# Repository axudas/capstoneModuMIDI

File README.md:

# ModuMIDI 2: Hall-Effect MIDI Keyboard (Capstone)

A modular MIDI keyboard that uses **magnetic (hall-effect) key switches** for analog, velocity-sensitive key sensing. The keyboard is built from identical 30-key **banks** that butt together flush, with the key pitch running straight across each seam. Each bank has its own RP2350 that reads its 30 sensors; a head unit (Adafruit Metro RP2350 with a 2.0" ST7789 display, encoder and buttons) collects the banks and sends USB-MIDI. This project builds on the original ModuMIDI (see `reference/original-modumidi`).

Portfolio page: [aidancarr.tech/modumidi.html](https://aidancarr.tech/modumidi.html)

## Repository layout

```
capstone/
├── README.md
├── design-notes.md            key design decisions and numbers
├── hardware/
│   ├── bank-board/            KiCad bank board (one per bank, 30 sensors, RP2350)
│   ├── bank-plate/            bank switch plate: laser-cut SVG, STEP, FreeCAD
│   ├── key-prototype/         one-key test stacks for the 3u white / black / grey keys: KiCad board, 3D models
│   ├── switch-test-rig/       FreeCAD switch-lifetime test rig (macro, FCStd, STEP, STLs)
│   └── kicad-library/         Capstone_Keyboard KiCad symbols, footprints, 3D models
├── firmware/                  firmware (bank firmware not started)
└── reference/
    └── original-modumidi/     original ModuMIDI: Altium PCB, 3D-printed parts, photos
```

## Status

| Area | Status |
|---|---|
| Parts library (KiCad) | ✅ Done. Needs a 1:1 paper-print fit check |
| Bank plate | ✅ Designed (SVG / STEP / FCStd), not cut yet |
| Bank board: schematic | 🟡 Complete first pass, all wired: RP2350A + flash, 12 V → 5 V → 3.3 V power, 4 analog muxes, 30 key-link connectors (LED chain + key presence), RS-485 bus. Netlist checked; ERC in KiCad 10 still to run |
| Bank board: layout | 🟡 Stepped bank outline, 6 mounting holes, all 214 parts placed (sensors, their capacitors and the key connectors on top; everything else on the bottom). Not routed |
| Head unit | 🟡 Metro RP2350 + display on the bench (see the design notebook); no board yet |
| Key prototype (1 key, 3u, RGB; white / black / grey) | 🟡 Shared board routed (DRC clean), models + cut files for all three keys, not built |
| Switch test rig | ✅ Designed, ready to print (servo dimensions need measuring) |
| Firmware | 🟡 Head-unit bring-up and 31-EDO MPE output tested (design notebook); bank firmware not started, nothing in `firmware/` yet |
| Enclosure / keycaps | ⬜ Not started |

## What's in each part

### Bank layout
Each bank has 30 keys in three rows (white at the front, black in the middle, grey at the back), 10 columns at a **22.86 mm (0.900 in)** pitch, with 3u stabilizers whose wires run front to back (14 × 7 mm housings). The rows are 48.90 mm apart so the white-rear / black-front and black-rear / grey-front housings sit side by side without touching. Banks repeat every **228.60 mm (9.000 in)**. A straight seam would cut through a cut-out, so the side edges have one step: a tab on the left drops into a notch on the right of the next bank. Details are in [design-notes.md](design-notes.md).

### Bank plate: `hardware/bank-plate`
1.5 mm switch plate for one bank (240.03 × 180.34 mm) with the stepped tab and notch, 30 switch cut-outs, 60 stabilizer cut-outs and 8 M3 holes. See its [README](hardware/bank-plate/README.md).

### Bank board: `hardware/bank-board`
One board per bank, shaped like the bank outline and trimmed front and back to the sensors and mounting holes (239.53 × 104.18 mm). 30 pick-and-place **DRV5055A4** hall sensors (SOT-23) sit under the switch centres and go through four analog muxes into the bank's own **RP2350A**. The board makes its own 5 V and 3.3 V from the 12 V on the inter-bank connector and talks to the head unit over RS-485. See its [README](hardware/bank-board/README.md) for every part and why it's there.

### Parts library: `hardware/kicad-library`
Custom KiCad symbols and footprints: RP2350A (QFN-60, from Raspberry Pi's reference design), hall sensors (SOT-23 and TO-92), magnetic MX switch, Cherry stabilizer holes, barrel jack, EC11 encoder, tactile switch, Metro RP2350 shield headers, ST7789 display header. Both KiCad projects already point to it. See its [README](hardware/kicad-library/README.md).

### Key prototype: `hardware/key-prototype`
Single-key test stacks for the three 3u bank keys (white, black, grey): one hand-solderable board shared by all three, foam, an acrylic plate with the bank plate's switch cut-out and Gateron low-profile stabilizer cut-outs (6.25u stabilizers, wire bent to 3u), a key with an LED pixel, and a magnetic diffuser topper with a top-detect pogo contact. See its [README](hardware/key-prototype/README.md).

### Switch lifetime test rig: `hardware/switch-test-rig`
A 3D-printable rig that presses a switch straight down over and over to measure its lifetime: micro servo, 2:1 gears, cam, roller and guided plunger. See its [README](hardware/switch-test-rig/README.md).

## Next steps

**Electronics**
- [ ] Fit-check the library footprints: print them 1:1 and push the real parts through.
- [ ] Run ERC on the bank schematic in KiCad 10.
- [ ] Choose the key-base wiring (flex or wires) and the blind-mate inter-bank header; both have placeholder footprints.
- [ ] Route the bank board, run DRC and order boards.
- [ ] Head-unit side of the bus: an RS-485 transceiver with fail-safe bias resistors.
- [ ] Check that the inner stabilizer housings clear the board under the plate (cut-outs in the board, or enough plate-to-PCB height).

**Firmware (`firmware/`)**
- [ ] Read the sensors through the muxes and calibrate each key (rest / bottom-out).
- [ ] Turn key travel into MIDI note on/off with velocity (and optionally aftertouch).
- [ ] MIDI output, display UI and encoder menu.

**Mechanical**
- [ ] Cut a bank plate and test the switch fit and the tab/notch tiling.
- [ ] Design the enclosure (it must follow the stepped plate profile) and the keycaps.
- [ ] Build the key prototypes (white, black, grey), measure a real Gateron low-profile stabilizer, and test its 12.5 × 6 mm cut-out and bent wire. Then update the bank plate's stabilizer cut-outs to match.

**Testing**
- [ ] Measure the SG51R servo, update the rig macro, then print and build the test rig.
- [ ] Write test-rig firmware (servo cycling, press counter, sensor logging) and run lifetime tests.

## Tools

- [KiCad](https://www.kicad.org) 10: schematics, boards and the parts library. Open `hardware/bank-board/moduMidi.kicad_pro` or `hardware/key-prototype/pcb/spacebarHall.kicad_pro`; the library tables are already set up.
- [FreeCAD](https://www.freecad.org) 1.1: bank plate and test rig.
- Python (manifold3d, trimesh, pyvista): key prototype models and renders.

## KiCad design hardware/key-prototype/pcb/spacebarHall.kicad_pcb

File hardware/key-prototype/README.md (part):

# Key prototype: one hall-effect key, 3u, RGB-lit (white / black / grey)

A single-key test stack for the ModuMIDI 2 bank keys. Each of the three key types has its own set of files: **white** (wide head at the front, narrow tail running back), **black** (narrow, centred on its switch) and **grey** (the white key turned around, head at the back). All three use the same board, switch, stabilizer and layer heights as the bank, and the plate cut-outs match [`bank-plate/ModuMIDI2_bank_plate.svg`](../bank-plate/README.md).

- A magnetic MX-style switch sits under the key, with a **Gateron low-profile plate-mounted stabilizer** (bought as 6.25u, wire cut and bent to 3u) whose housings are 19.05 mm in front of and behind the switch. The key runs front to back.
- One RGB pixel cut from a 5 mm WS2812B-2020 strip sits in a pocket in the key and shines up into a thin, hollow, diffusing topper.
- The topper locates with a lip all round that hugs the top of the key, and is held on by two magnets.
- A 2-pin pogo connector in the key is shorted by a brass shim in the topper, so the controller can tell whether the topper is on.
- Everything on the board is **hand-solderable** through-hole.

Each stack on its own: [white](img/exploded_white.png), [black](img/exploded_black.png), [grey](img/exploded_grey.png).

## Key sizes

Cap outlines from the bank drawing, measured from the key's switch centre (y = toward the back):

| Key | Outline | Switch |
|---|---|---|
| White | Head 20.32 mm wide from y −28.58 to +17.78, tail 6.35 mm wide from +17.78 to +47.63 (76.2 mm long) | 28.58 mm from the front end |
| Black | 11.43 × 57.15 mm, y −28.58 to +28.58 | centred |
| Grey | The white key turned 180°: head from −17.78 to +28.58, tail from −47.63 to −17.78 | 28.58 mm from the back end |

All keys are 12 mm tall with steep walls (the top is 0.6 mm in from the bottom edge all round).

## Layer stack (bottom → top)

| # | Layer | Size | Notes |
|---|---|---|---|
| 1 | **PCB** | 1.6 mm | 30 × 113 mm, shared by all three keys. **U1** TO-92 hall sensor lies flat under the switch centre. **C1** 100 nF axial. **R1** 330 Ω (LED data), **R3** 10 kΩ pull-up (top detect). **J2** 5-pin key header 11.35 mm behind the switch (DI, DET, GND, DO, 5V: the five wires up to the key). **J1** 7-way 3.5 mm screw terminal on a 13 mm tab that sticks out past the foam and plate. |
| 2 | **Foam** | 3.5 mm | Fills the gap between PCB and plate. Cut-outs for the switch, stabilizer housings, wire and wire arms, C1/R1/R3, and the J2 header. |
| 3 | **Acrylic plate** | 1.5 mm | 14.00 mm switch cut-out and two **12.5 × 6.0 mm** low-profile stabilizer cut-outs (Gateron's drawing) 19.05 mm in front of and behind it. **A 1.7 mm slot for the stabilizer wire** runs from each housing's notch out to the bar and along the bar, 9.5 mm to the side of the switch (a U joining the two housings): the wire drops into the slot, the bar pivots there and the arms go through the notches into the sliders. Plus a 12.7 × 2.6 mm slot over J2 for the key's five wires. Each opening is one closed outline in the DXF. |
| 4 | **Key** | 12 mm tall | Centre MX stem socket, and 2 **stabilizer posts** on the centre line that reach down to the low-profile stabilizer (it sits much lower than the full-height switch; the posts stick out below the narrow white/grey tail). On top: **LED pocket** (strip piece + wire bay over the wire hole), **pogo connector pocket** (pins up), **2 magnet pockets**. Underneath: a relief for the switch top housing (the black key is narrower than the switch). |
| 4a | **RGB LED** | 5 × 6.9 mm | **One pixel cut from a 5 mm wide, 144 LED/m WS2812B-2020 strip.** Solder DI, 5V and GND to its DIN-end pads and DO to its DOUT-end pad (lay the DO wire back along the edge of the strip, beside the LED body, to the wire bay). All wires drop through the key's wire hole and the plate slot to J2. |
| 4c | **Pogo connector** | 9.6 × 3.2 mm body (estimated), 5.80 mm pitch | [Top-Link 10101022778](https://www.hktop-link.com/shop/pogo-pin-connectors/2pin-pogo-pin-connector.html), its pin row along the key. The plungers stick up 1 mm above the key top. With the topper on they press flush onto the shim, which shorts them: **TOP_DET goes low = top is on**. Its two wires run inside the key to the LED end: DET down to J2, GND jumped to the LED's GND pad. |
| 5 | **Topper** | **5 mm tall, hollow** | 2 mm walls, 1.0 mm diffuser top, open over the LED. Solid blocks hold **two 6 × 2 mm magnets** and the **4 × 9 mm brass shim** (or copper tape) that shorts the pogo pins. A **1 mm lip** all round reaches 2 mm down the key's sides and locates the topper; the magnets only line up one way round. The topper covers the white/grey tail as a solid strip. |

| Key | LED (wire hole) | Pogo | Magnets |
|---|---|---|---|
| Black | 11.35 mm behind the switch | 11.35 mm in front | on the centre line, 24 mm in front and behind |
| Grey | 11.35 mm behind the switch (in the head) | 11.35 mm in front (where the head meets the tail) | 24 mm behind, and 5.5 mm to the right of the pogo |
| White | the grey layout turned around: LED in front of the switch, pogo behind it | | |

**One board for all three keys.** Black and grey use it as drawn. The white key is the grey key turned around, so the **whole white stack is the grey stack rotated 180°, board included**, and its terminal tab ends up at the front.

The foam and plate are 30 × 100 mm. All three layers share 4 × M2 holes at (±12, ±47) mm. Heights follow the MX spec: plate top is 5.0 mm above PCB top. Key travel is **3.5 mm**, set by the low-profile stabilizer (estimated; the MX switch has 4 mm). A fully pressed key clears the plate, the switch housing and the stabilizer housings, and the stabilizer sliders stay clear of the PCB (checked in the model for all three keys).

## Parts to buy, per key (besides PCB, acrylic, foam, prints)

| Qty | Part |
|---|---|
| 1 | MX-style magnetic switch (e.g. Gateron KS-20), no centre post |
| 1 | [Gateron low-profile plate-mounted stabilizer, 6.25u](https://www.gateron.com/products/gateron-low-profile-plate-mounted-stabilizer?VariantsId=10478): cut and bend the wire so the housings are 38.1 mm apart |
| 1 | Linear hall sensor TO-92: SS49E / 49E, or DRV5055A4QLPG |
| 1 | 100 nF axial ceramic capacitor (about 2 × 4 mm body, 7.62 mm lead spacing) |
| 1 | 330 Ω 1/8 W axial resistor (0204 size) |
| 1 | 10 kΩ 1/8 W axial resistor (0204 size), TOP_DET pull-up |
| 1 | 7-way PCB screw terminal, 3.5 mm pitch, horizontal wire entry (Phoenix PT 1,5/7-3,5-H or a generic "KF350-7P") |
| 1 | 1 × 5 pin header, 2.54 mm (J2); trim the pins to about 1 mm above the plate |
| 1 pixel | WS2812B-2020 strip, 5 mm wide, 144 LED/m (cut one pixel at the copper cut lines) |
| ~20 cm | 30 AWG silicone wire: 5 from J2 up to the key (DI, DET, GND, DO, 5V; leave a slack loop for the key travel) + 1 short GND jumper from the LED to the pogo connector |
| 4 | 6 × 2 mm neodymium disc magnets |
| 1 | 2-pin pogo pin connector, 5.80 mm pitch (Top-Link 10101022778) |
| 1 | 4 × 9 mm piece of 0.3 mm brass shim, or conductive copper tape |
| 4 | M2 screws + nuts / standoffs |

## Folder contents

```
key-prototype/
├── pcb/                       KiCad project (schematic + routed 2-layer board, schematic PDF), shared by all keys
├── mechanical/
│   ├── spacebar_stack.py       parametric source for every part and all three keys (edit numbers at the top, re-run)
│   ├── render_views.py         renders the PNGs in img/ (pyvista)
│   ├── white/                  one folder per key type, each with:
│   ├── black/                    stack_exploded.stl/.glb   the whole design broken apart (GLB coloured per part)
│   └── grey/                     stack_assembled.stl/.glb  everything in its assembled position
│                                 key_assembled.stl/.glb    the key + topper + LED, pogo, magnets, shim
│                                 key_exploded.stl/.glb     the same key broken apart
│                                 stl/                      one STL per part
│                                 cut-files/                DXF outlines for laser-cutting the plate and the foam
└── img/                        renders, KiCad PCB layout + schematic images
```

## PCB: `pcb/spacebarHall.kicad_pro` (KiCad)

Open it in KiCad 7 or newer. The schematic is also saved as `spacebarHall_schematic.pdf`. Positions are from the switch centre, y toward the back of the key.

| Ref | Part | Footprint / position |
|---|---|---|
| U1 | TO-92 linear hall sensor | `Capstone_Keyboard:Hall_TO-92_LyingFlat`. Bend the leads 90° about 1.5 mm below the body and lay it **branded face up**, body centre under the magnet. Pads 3 mm to the left. |
| K1 | Magnetic switch | `Capstone_Keyboard:MX_Magnetic_NoCenterPost` (peg holes at ±5.08 mm) |
| C1 | 100 nF axial | `C_Axial_L3.8mm_D2.6mm_P7.50mm_Horizontal`, at x = +9.5 (lying flat, in the foam cut-out) |
| R1 | 330 Ω axial | `R_Axial_DIN0204…`, LED data, at x = −13, y = +24.5…+32.1 |
| R3 | 10 kΩ axial, TOP_DET → 3V3 | `R_Axial_DIN0204…`, at y = +36 |
| J2 | Key header, left to right: **1 DI / 2 DET / 3 GND / 4 DO / 5 5V** | `PinHeader_1x05_P2.54mm_Vertical` at y = +11.35, under the LED wire hole and the plate slot. The header body sits in the foam; trim the pins to about 1 mm above the plate (full-length pins would touch the black key when pressed) and solder the key's wires to them |
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
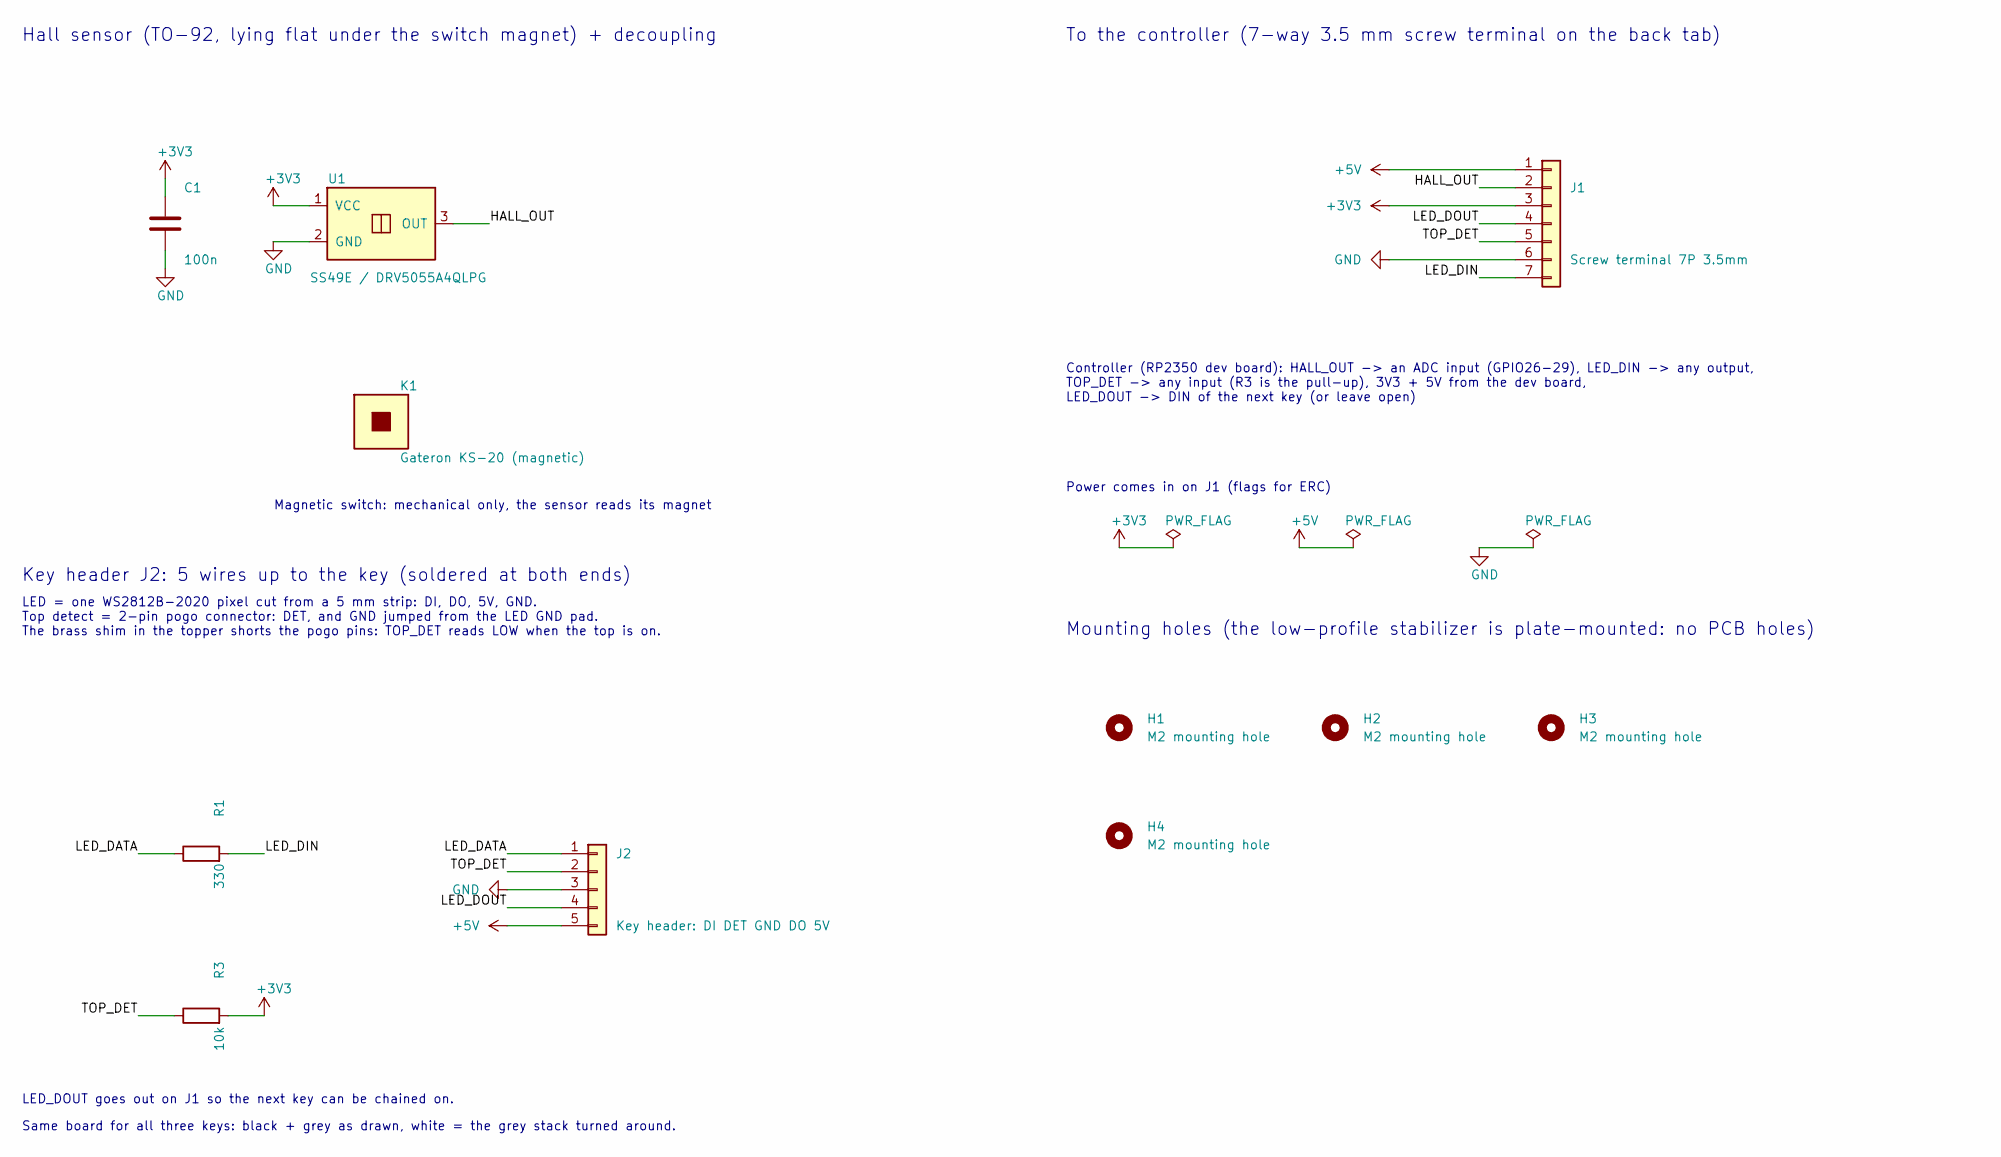
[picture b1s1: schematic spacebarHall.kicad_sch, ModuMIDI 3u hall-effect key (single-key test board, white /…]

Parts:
C1: 100n; C_Axial_L3.8mm_D2.6mm_P7.50mm_Horizontal
H1, H2, H3, H4: M2 mounting hole; MountingHole_2.2mm_M2
J1: Screw terminal 7P 3.5mm; TerminalBlock_Phoenix_PT-1,5-7-3.5-H_1x07_P3.50mm_Horizontal
J2: Key header: DI DET GND DO 5V; PinHeader_1x05_P2.54mm_Vertical
K1: Gateron KS-20 (magnetic); MX_Magnetic_NoCenterPost
R1: 330; R_Axial_DIN0204_L3.6mm_D1.6mm_P7.62mm_Horizontal
R3: 10k; R_Axial_DIN0204_L3.6mm_D1.6mm_P7.62mm_Horizontal
U1: SS49E / DRV5055A4QLPG; Hall_TO-92_LyingFlat

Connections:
+3V3: C1.1, J1.3, R3.2, U1.1 (VCC)
+5V: J1.1, J2.5
GND: C1.2, J1.6, J2.3, U1.2 (GND)
HALL_OUT: J1.2, U1.3 (OUT)
LED_DATA: J2.1, R1.1
LED_DIN: J1.7, R1.2
LED_DOUT: J1.4, J2.4
TOP_DET: J1.5, J2.2, R3.1

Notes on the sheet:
Hall sensor (TO-92, lying flat under the switch magnet) + decoupling
Magnetic switch: mechanical only, the sensor reads its magnet
Key header J2: 5 wires up to the key (soldered at both ends)
LED = one WS2812B-2020 pixel cut from a 5 mm strip: DI, DO, 5V, GND. Top detect = 2-pin pogo connector: DET, and GND jumped from the LED GND pad. The brass shim in the topper shorts the pogo pins: TOP_DET reads LOW when the top is on.
LED_DOUT goes out on J1 so the next key can be chained on.
Same board for all three keys: black + grey as drawn, white = the grey stack turned around.
To the controller (7-way 3.5 mm screw terminal on the back tab)
Controller (RP2350 dev board): HALL_OUT -> an ADC input (GPIO26-29), LED_DIN -> any output, TOP_DET -> any input (R3 is the pull-up), 3V3 + 5V from the dev board, LED_DOUT -> DIN of the next key (or leave open)
Power comes in on J1 (flags for ERC)
Mounting holes (the low-profile stabilizer is plate-mounted: no PCB holes)

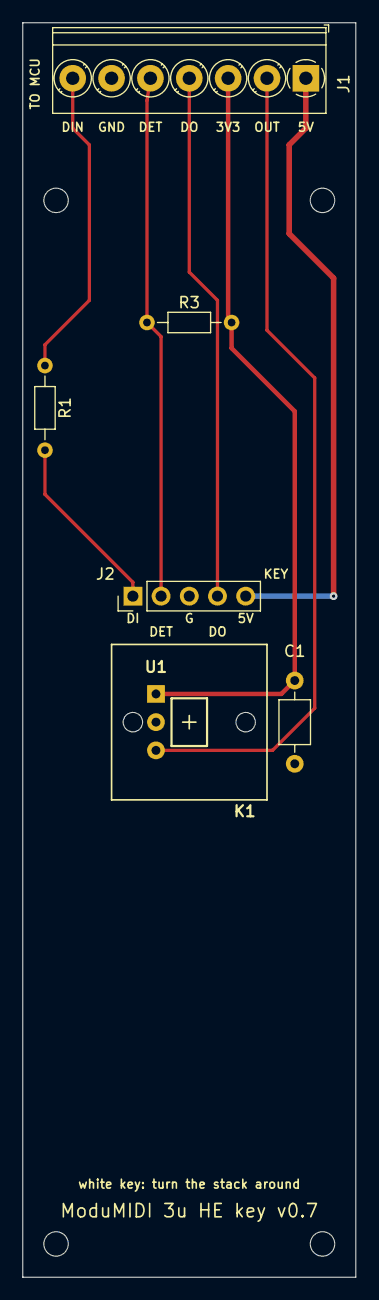
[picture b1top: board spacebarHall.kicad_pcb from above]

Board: 2 copper layers, 30.0 x 113.0 mm, 11 parts (0 on the bottom side), 8 nets.

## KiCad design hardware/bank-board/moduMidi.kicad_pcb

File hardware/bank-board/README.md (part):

# moduMidi: bank board (KiCad)

The **bank board** of the ModuMIDI 2 hall-effect keyboard: one board per bank, 30 keys, with its own RP2350. Open `moduMidi.kicad_pro` in KiCad 10. Parts come from `../kicad-library/Capstone_Keyboard` (already set up in this project's library tables) and the standard KiCad libraries.

## Schematic

Six sheets. They connect through global labels and power symbols, so a net has the same name on every sheet.

| Sheet | File | What's on it |
|---|---|---|
| Root | `moduMidi.kicad_sch` | 30 DRV5055 hall sensors with one 100 nF each |
| MCU | `bank_mcu.kicad_sch` | RP2350A with its flash, crystal, core regulator, boot/run buttons, SWD and USB service connectors |
| Power | `bank_power.kicad_sch` | Inter-bank connectors, 12 V → 5 V buck, two 3.3 V LDOs, power-good LEDs, rail monitors |
| Muxes | `bank_mux.kicad_sch` | Four CD74HC4067 analog multiplexers |
| Key links | `bank_keys.kicad_sch` | LED data buffer and one connector per key (LED chain + key presence) |
| Bus | `bank_bus.kicad_sch` | RS-485 transceiver, termination jumper, bank address jumpers |

**Numbering:** sensor n is Un, its capacitor C1nn, its presence pull-up R1nn and its key connector J1nn (for example key 7: U7, C107, R107, J107).

### Power rails

| Rail | From | Feeds |
|---|---|---|
| +12V | Inter-bank connector J3, passed on through J4 | Buck, rail monitor |
| +5V | U33 buck (3 A) | Key LEDs, LED buffer, both LDOs |
| +3V3 | U34 LDO | RP2350 IO, flash, RS-485 |
| +3.3VA | U35 LDO behind ferrite bead FB1 | 30 sensors, 4 muxes, RP2350 ADC (ADC_AVDD) |
| +1V1 | RP2350's own core regulator (L1) | RP2350 core (DVDD) |

### RP2350A pins used

| GPIO | Net | Use |
|---|---|---|
| 0 / 1 / 2 | BUS_TX / BUS_RX / BUS_DE | UART0 to the RS-485 transceiver |
| 3 / 4 | BANK_ID0 / BANK_ID1 | Bank address jumpers (internal pull-ups) |
| 6–9 | MUX_S0–S3 | Select lines, shared by all four muxes |
| 10 | LED_DATA | Key LED chain (through the 5 V buffer) |
| 25 | STATUS_LED | Status LED D1 |
| 26 / 27 | ADC_KEY_A / ADC_KEY_B | Key sensors 1–15 / 16–30 |
| 28 / 29 | ADC_DET_A / ADC_DET_B | Key presence 1–15 / 16–30 |

GPIO5 and GPIO11–24 are unused (no-connect flags).

## Parts list

### Root: sensors
| Ref | Part | Why |
|---|---|---|
| U1–U30 | DRV5055A4QDBZR, SOT-23 | One linear hall sensor under each switch. The A3 fits the same footprint if the bench test picks it. |
| C101–C130 | 100 nF 0402 | Decoupling right at each sensor. |

### MCU (from Raspberry Pi's RP2350A minimal design)
| Ref | Part | Why |
|---|---|---|
| U31 | RP2350A, QFN-60 | The bank's own controller (notebook p. 28). Scans the 30 keys through the muxes and reports to the head unit. |
| U32 | W25Q128JVS QSPI flash, SOIC-8 | Program storage; the RP2350 has no internal flash. A smaller W25Q16/W25Q32 works too. |
| Y1, C2, C3, R1 | 12 MHz ABM8-272-T3, 2 × 15 pF, 1 kΩ | Clock crystal with load caps; R1 limits drive, as in the reference design. |
| L1 | 3.3 µH, 2016, polarised | Core-regulator inductor (VREG_LX → +1V1). Keep the footprint's dot orientation. |
| R2, C4 | 33 Ω, 4.7 µF | Filter for VREG_AVDD. |
| C5–C9 | 4.7 µF × 4, 100 nF × 2 | VREG_VIN and +1V1 (DVDD) decoupling. |
| C10–C17, C18 | 100 nF × 8, 10 µF | One per IOVDD / QSPI_IOVDD / USB_OTP_VDD pin, plus bulk. |
| C19 | 100 nF | ADC_AVDD (on +3.3VA). |
| C1 | 100 nF | Flash decoupling. |
| SW1, R3 | Push button, 1 kΩ | BOOTSEL: hold while resetting to get the USB bootloader. |
| SW2, R4 | Push button, 1 kΩ | RUN (reset). |
| J1 | JST SH 3-pin | Raspberry Pi debug connector (SWD) for the Debug Probe. |
| J2, R5, R6 | JST SH 4-pin, 2 × 27 Ω | USB service port for bench bring-up and UF2 flashing. Pin 1 (VBUS) isn't used. |
| D1, R7 | LED, 1 kΩ | Status LED on GPIO25. |

### Power
| Ref | Part | Why |
|---|---|---|
| J3 / J4 | 2 × 6, 2.54 mm SMD socket / header | Inter-bank connector in and out (notebook p. 28: 12 pins, 12 V and return on several pins each, bus pair). SMD on the bottom side so no pins come up into the switches; placeholder footprints until the blind-mate header is chosen. |
| D2 | SMAJ15A TVS | Clamps 12 V spikes when a bank is plugged in live. |
| C20 | 47 µF 25 V electrolytic | Damps the ringing of the cable inductance on hot-plug. |
| C21–C23 | 2 × 10 µF 25 V, 100 nF | Buck input capacitors. |
| U33 | TPS54302, SOT-23-6 | 12 V → 5 V buck, 3 A. Local regulation per bank (notebook p. 22): a worn connector loses volts, not LED brightness. |
| R8, R9 | 100 kΩ, 20 kΩ | Enable divider: the buck starts above about 7 V and EN stays at 2 V. |
| C24 | 100 nF | Bootstrap capacitor. |
| L2 | 10 µH, Bourns SRN6045TA | Buck inductor. |
| R10, R11 | 100 kΩ, 13.3 kΩ | Feedback divider: 0.596 V × (1 + 100/13.3) = 5.08 V. |
| C25–C27 | 2 × 22 µF 10 V, 100 µF 10 V electrolytic | Buck output and LED-rail reservoir. |
| U34, C28, C29 | AP2112K-3.3, 1 µF, 10 µF | +3V3 digital LDO. |
| FB1 | Ferrite bead, 600 Ω at 100 MHz, 0805 | Keeps buck ripple and LED current off the analog LDO. |
| U35, C30–C32 | AP7361C-33E (SOT-223), 2 × 10 µF, 100 nF | +3.3VA analog LDO: sensors, muxes, ADC (about 0.2–0.3 A). |
| D3–D6, R12–R15 | Green 0603 LEDs, 10 k / 2.2 k / 1 k / 1 kΩ | Power-good LED on every rail (notebook p. 42). |
| R16, R17, C33 | 100 kΩ, 27 kΩ, 100 nF | V12_SENSE: 12 V monitor, reads up to 15.5 V (notebook p. 23). |
| R18, R19, C34 | 100 kΩ, 100 kΩ, 100 nF | V5_SENSE: 5 V monitor. |

### Muxes
| Ref | Part | Why |
|---|---|---|
| U36, U37 | CD74HC4067M | Keys 1–15 and 16–30 into ADC0/ADC1. Channel 15 carries V12_SENSE / V5_SENSE. |
| U38, U39 | CD74HC4067M | Presence 1–15 and 16–30 into ADC2/ADC3. Channel 15 is tied to GND as a zero check. |
| C35–C38 | 100 nF | Mux decoupling. |

All four share MUX_S0–S3, so one select step reads key n, key n+15 and both presence lines.

### Key links
| Ref | Part | Why |
|---|---|---|
| U40 | 74AHCT1G125, SOT-23-5 | Re-drives the 3.3 V LED data at 5 V for the WS2812 chain (notebook p. 23). |
| C39, R20, R21 | 100 nF, 10 kΩ pull-down, 330 Ω | Decoupling; keeps LED data low while the RP2350 boots; series resistor at the chain input. |
| J101–J130 | 5-pin connector per key | Key-base link: 1 +5V, 2 GND, 3 LED DIN, 4 LED DOUT, 5 DET. The LED sits in the key base (Tier 1) and two pogo pins report whether the cap is on (notebook p. 29). JST SH footprint is a placeholder until the key-base wiring is chosen. |
| R101–R130 | 10 kΩ | Pull DET up to +3.3VA: high = cap off, low = cap on. |
| TP1 | Test pad | End of the LED chain (LED_CH31). |

### Bus
| Ref | Part | Why |
|---|---|---|
| U41 | MAX3485, SOIC-8 | 3.3 V half-duplex RS-485 on the connector's bus pair; robust over the bank chain. |
| C40 | 100 nF | Decoupling. |
| R22 | 10 kΩ | Holds DE low (receive) while the RP2350 boots. |
| JP1, R23 | Solder jumper, 120 Ω | Bus termination: close on the last bank only. |
| JP2, JP3 | Solder jumpers | Bank address 0–3, like the 2023 boards' solder bridges. |

### Removed
- **J1 DC jack:** the 12 V supply plugs into the head unit and reaches the banks over the inter-bank connector (notebook p. 28), so banks don't need their own jack.

### Not added, and why
- **Op-amp buffer and separate analog ground return** (notebook p. 23): these were for sending analog signals to the head unit. With an RP2350 on every bank the analog path stays on the board.
- **Reverse-polarity FET and fuse** (notebook p. 21): they belong at the head unit's 12 V input, where the supply plugs in.

## Board

- **Outline:** the bank outline (one step each way: tab on the left, notch on the right; side edges and steps inset 0.25 mm) trimmed front and back to the smallest band that holds the 30 sensors and 6 mounting holes (+1 mm). **239.53 × 104.18 mm**, outer corners R3, step corners R1.
  - Boards tile with a 0.5 mm gap, and each board stays inside its own bank's footprint (black column 1's sensor sits in the tab).
  - The full plate outline and its dimensions are on the **Bank.Outline** layer (User.1), for reference.
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
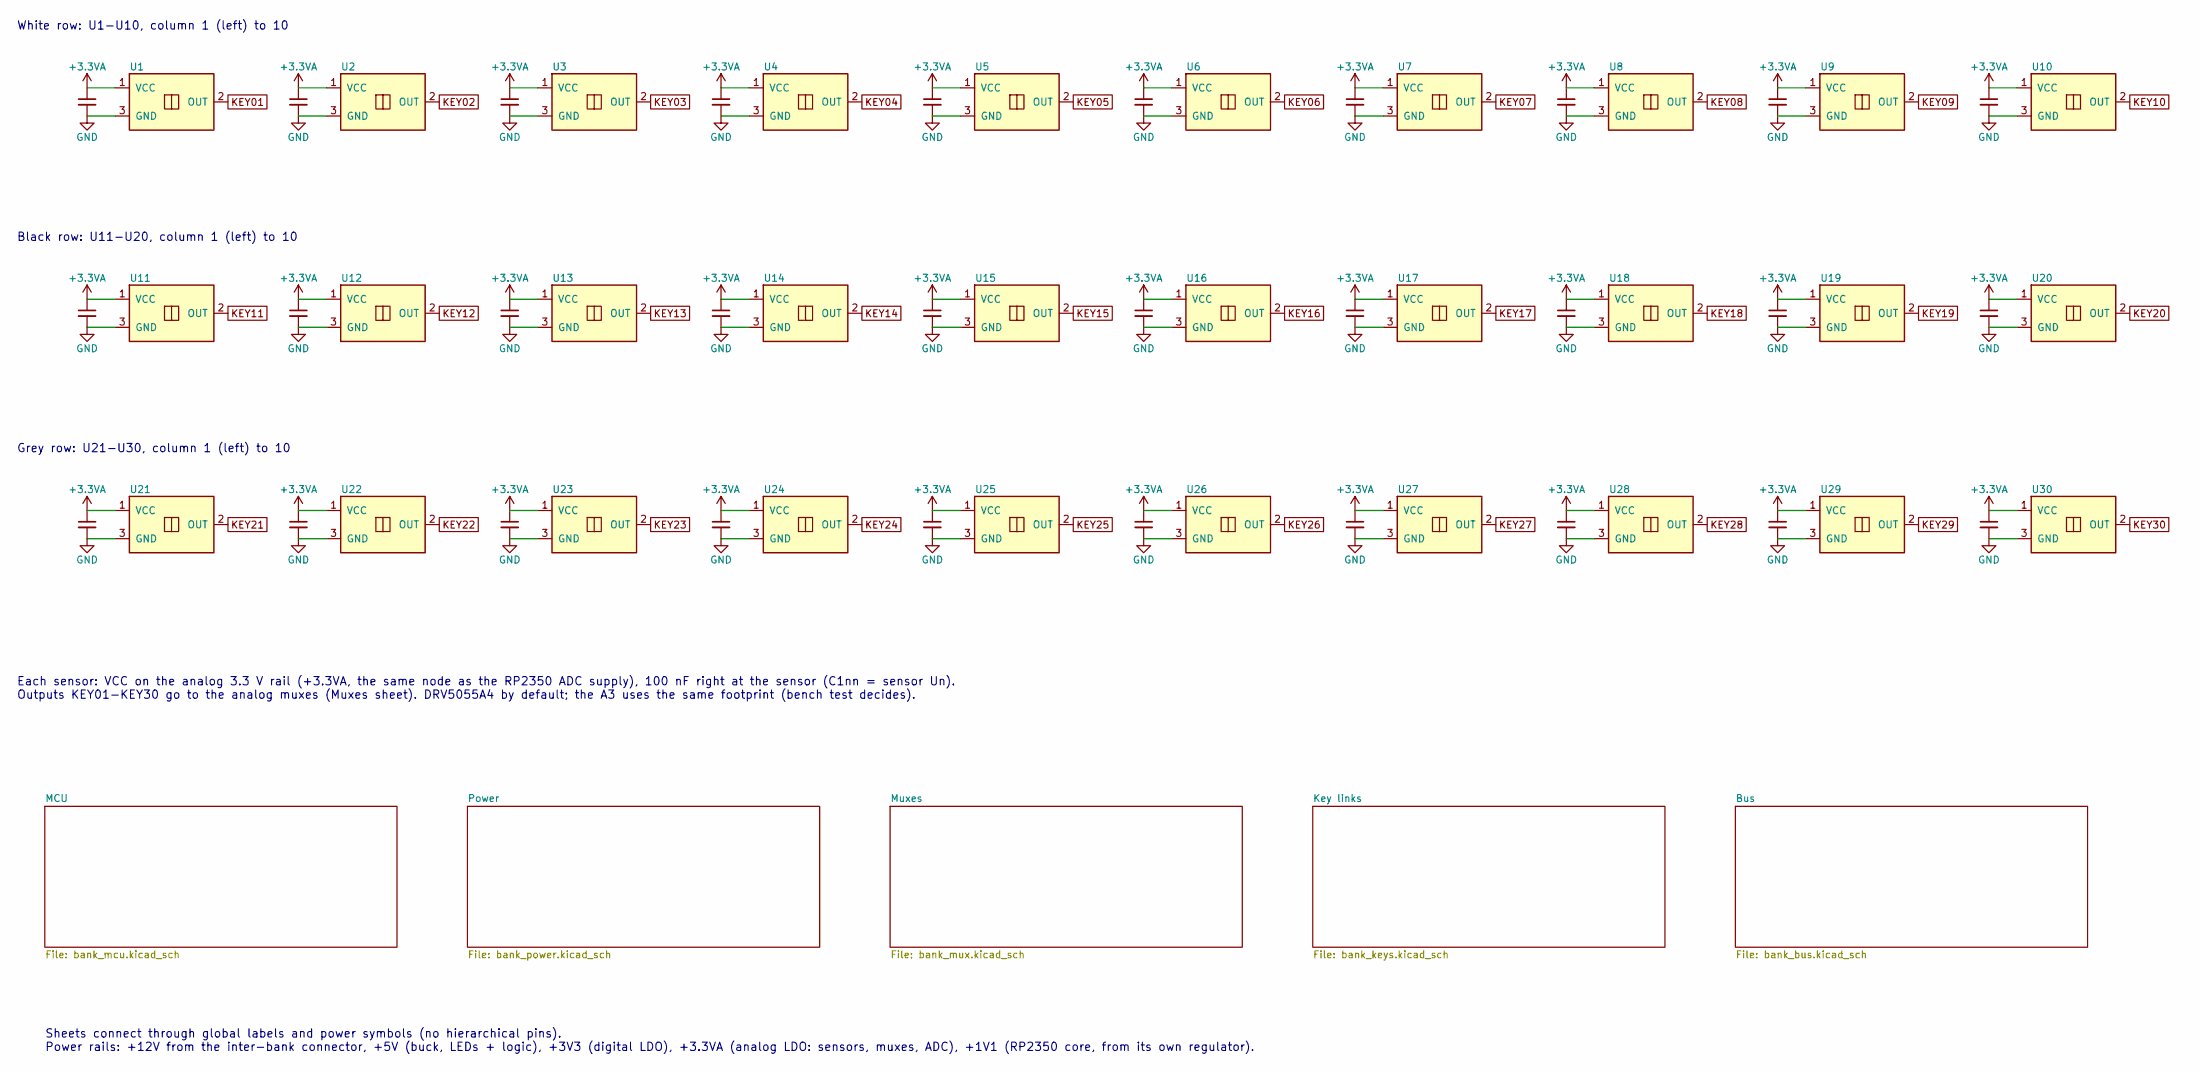
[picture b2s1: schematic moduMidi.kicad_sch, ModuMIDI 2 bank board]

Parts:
C101, C102, C103, C104, C105, C106, C107, C108, C109, C110, C111, C112, C113, C114, C115, C116, C117, C118, C119, C120, C121, C122, C123, C124, C125, C126, C127, C128, C129, C130: 100n; C_0402_1005Metric
U1, U2, U3, U4, U5, U6, U7, U8, U9, U10, U11, U12, U13, U14, U15, U16, U17, U18, U19, U20, U21, U22, U23, U24, U25, U26, U27, U28, U29, U30: DRV5055A4QDBZR; Hall_SOT-23-3

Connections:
+3.3VA: C101.1, C102.1, C103.1, C104.1, C105.1, C106.1, C107.1, C108.1, C109.1, C110.1, C111.1, C112.1, C113.1, C114.1, C115.1, C116.1, C117.1, C118.1, C119.1, C120.1, C121.1, C122.1, C123.1, C124.1, C125.1, C126.1, C127.1, C128.1, C129.1, C130.1, U1.1 (VCC), U2.1 (VCC), U3.1 (VCC), U4.1 (VCC), U5.1 (VCC), U6.1 (VCC), U7.1 (VCC), U8.1 (VCC), U9.1 (VCC), U10.1 (VCC), U11.1 (VCC), U12.1 (VCC), U13.1 (VCC), U14.1 (VCC), U15.1 (VCC), U16.1 (VCC), U17.1 (VCC), U18.1 (VCC), U19.1 (VCC), U20.1 (VCC), U21.1 (VCC), U22.1 (VCC), U23.1 (VCC), U24.1 (VCC), U25.1 (VCC), U26.1 (VCC), U27.1 (VCC), U28.1 (VCC), U29.1 (VCC), U30.1 (VCC); also elsewhere on the board
GND: C101.2, C102.2, C103.2, C104.2, C105.2, C106.2, C107.2, C108.2, C109.2, C110.2, C111.2, C112.2, C113.2, C114.2, C115.2, C116.2, C117.2, C118.2, C119.2, C120.2, C121.2, C122.2, C123.2, C124.2, C125.2, C126.2, C127.2, C128.2, C129.2, C130.2, U1.3 (GND), U2.3 (GND), U3.3 (GND), U4.3 (GND), U5.3 (GND), U6.3 (GND), U7.3 (GND), U8.3 (GND), U9.3 (GND), U10.3 (GND), U11.3 (GND), U12.3 (GND), U13.3 (GND), U14.3 (GND), U15.3 (GND), U16.3 (GND), U17.3 (GND), U18.3 (GND), U19.3 (GND), U20.3 (GND), U21.3 (GND), U22.3 (GND), U23.3 (GND), U24.3 (GND), U25.3 (GND), U26.3 (GND), U27.3 (GND), U28.3 (GND), U29.3 (GND), U30.3 (GND); also elsewhere on the board
KEY01: U1.2 (OUT); also elsewhere on the board
KEY02: U2.2 (OUT); also elsewhere on the board
KEY03: U3.2 (OUT); also elsewhere on the board
KEY04: U4.2 (OUT); also elsewhere on the board
KEY05: U5.2 (OUT); also elsewhere on the board
KEY06: U6.2 (OUT); also elsewhere on the board
KEY07: U7.2 (OUT); also elsewhere on the board
KEY08: U8.2 (OUT); also elsewhere on the board
KEY09: U9.2 (OUT); also elsewhere on the board
KEY10: U10.2 (OUT); also elsewhere on the board
KEY11: U11.2 (OUT); also elsewhere on the board
KEY12: U12.2 (OUT); also elsewhere on the board
KEY13: U13.2 (OUT); also elsewhere on the board
KEY14: U14.2 (OUT); also elsewhere on the board
KEY15: U15.2 (OUT); also elsewhere on the board
KEY16: U16.2 (OUT); also elsewhere on the board
KEY17: U17.2 (OUT); also elsewhere on the board
KEY18: U18.2 (OUT); also elsewhere on the board
KEY19: U19.2 (OUT); also elsewhere on the board
KEY20: U20.2 (OUT); also elsewhere on the board
KEY21: U21.2 (OUT); also elsewhere on the board
KEY22: U22.2 (OUT); also elsewhere on the board
KEY23: U23.2 (OUT); also elsewhere on the board
KEY24: U24.2 (OUT); also elsewhere on the board
KEY25: U25.2 (OUT); also elsewhere on the board
KEY26: U26.2 (OUT); also elsewhere on the board
KEY27: U27.2 (OUT); also elsewhere on the board
KEY28: U28.2 (OUT); also elsewhere on the board
KEY29: U29.2 (OUT); also elsewhere on the board
KEY30: U30.2 (OUT); also elsewhere on the board

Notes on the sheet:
White row: U1-U10, column 1 (left) to 10
Black row: U11-U20, column 1 (left) to 10
Grey row: U21-U30, column 1 (left) to 10
Each sensor: VCC on the analog 3.3 V rail (+3.3VA, the same node as the RP2350 ADC supply), 100 nF right at the sensor (C1nn = sensor Un). Outputs KEY01-KEY30 go to the analog muxes (Muxes sheet). DRV5055A4 by default; the A3 uses the same footprint (bench test decides).
Sheets connect through global labels and power symbols (no hierarchical pins). Power rails: +12V from the inter-bank connector, +5V (buck, LEDs + logic), +3V3 (digital LDO), +3.3VA (analog LDO: sensors, muxes, ADC), +1V1 (RP2350 core, from its own regulator).

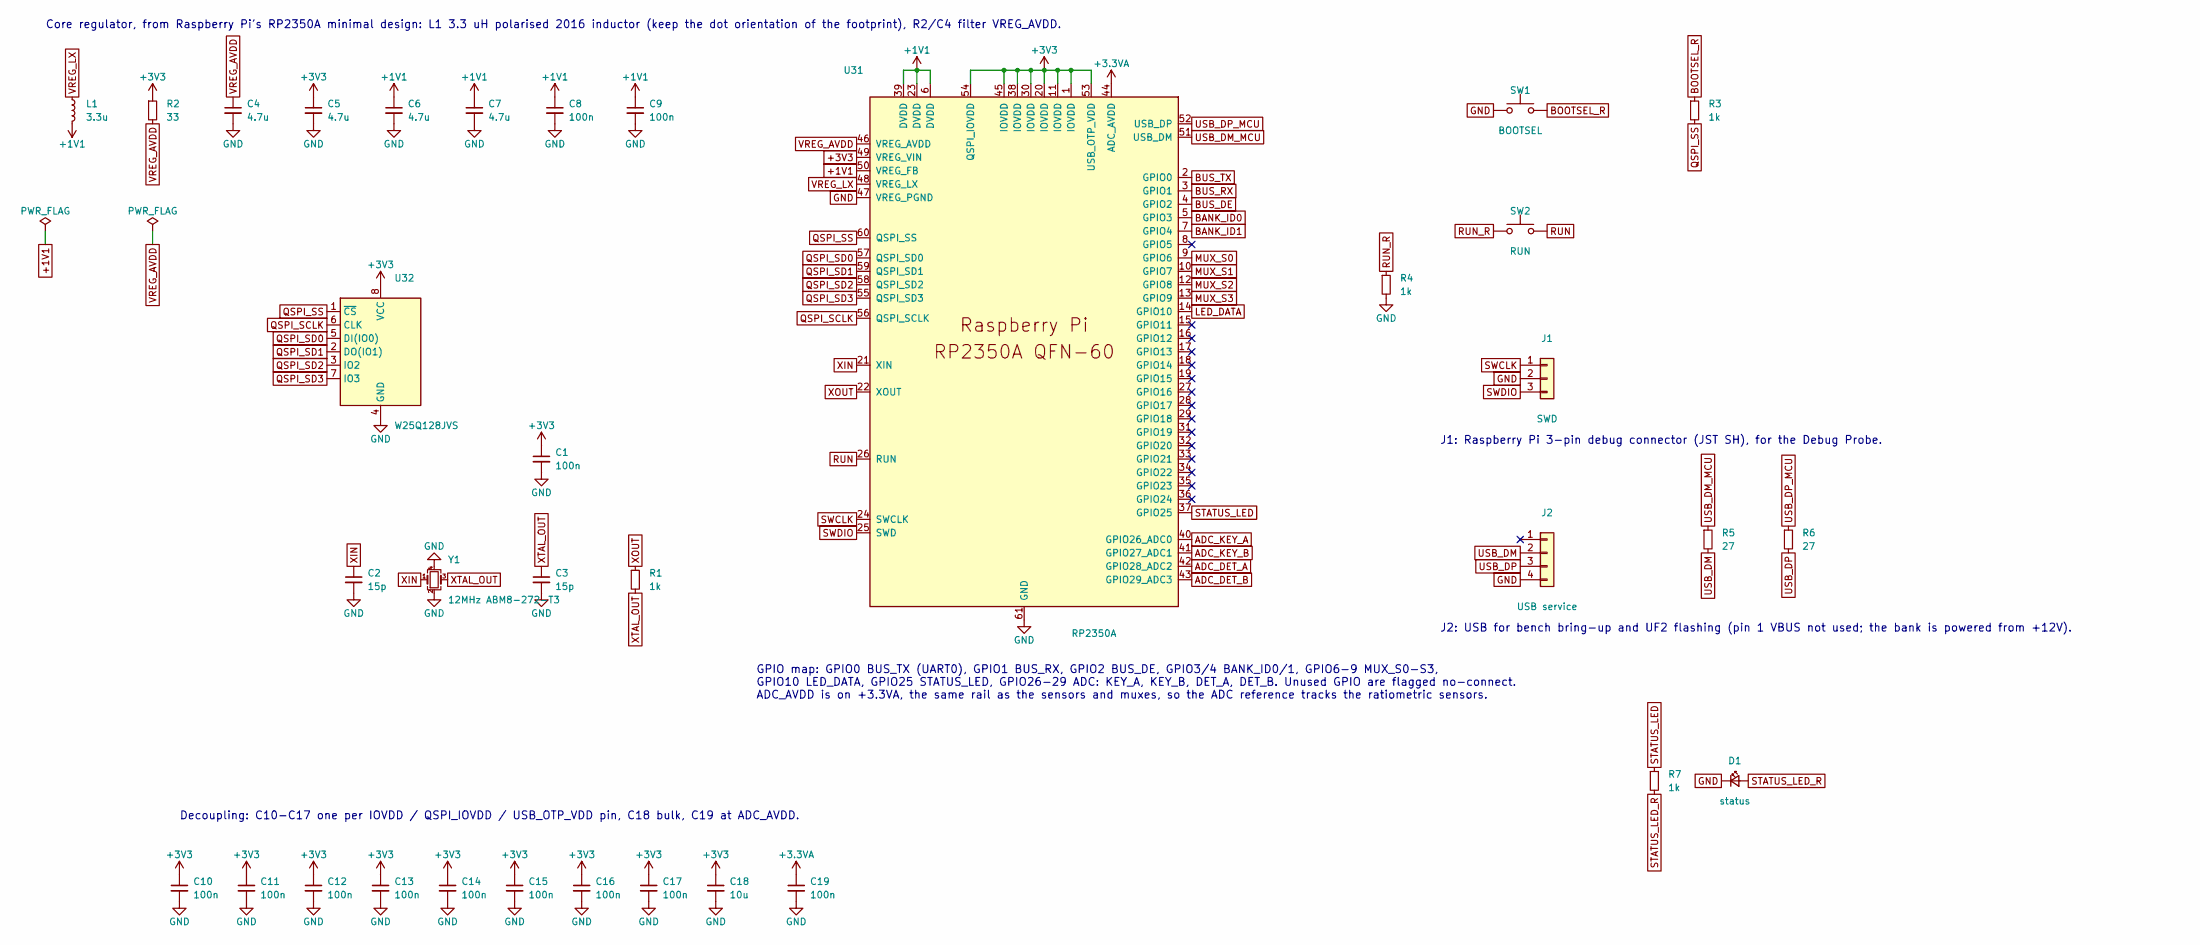
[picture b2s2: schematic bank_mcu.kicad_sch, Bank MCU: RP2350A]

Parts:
C1, C8, C9, C10, C11, C12, C13, C14, C15, C16, C17, C19: 100n; C_0402_1005Metric
C2, C3: 15p; C_0402_1005Metric
C4, C5, C6, C7: 4.7u; C_0402_1005Metric
C18: 10u; C_0805_2012Metric
D1: status; LED_0603_1608Metric
J1: SWD; JST_SH_SM03B-SRSS-TB_1x03-1MP_P1.00mm_Horizontal
J2: USB service; JST_SH_SM04B-SRSS-TB_1x04-1MP_P1.00mm_Horizontal
L1: 3.3u; L_pol_2016
R1, R3, R4, R7: 1k; R_0402_1005Metric
R2: 33; R_0402_1005Metric
R5, R6: 27; R_0402_1005Metric
SW1: BOOTSEL; SW_Push_1P1T_NO_Vertical_Wuerth_434133025816
SW2: RUN; SW_Push_1P1T_NO_Vertical_Wuerth_434133025816
U31: RP2350A; RP2350-QFN-60-1EP_7x7_P0.4mm_EP3.4x3.4mm_ThermalVias
U32: W25Q128JVS; SOIC-8_5.23x5.23mm_P1.27mm
Y1: 12MHz ABM8-272-T3; Crystal_SMD_3225-4Pin_3.2x2.5mm

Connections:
+1V1: C6.1, C7.1, C8.1, C9.1, L1.2, U31.6 (DVDD), U31.23 (DVDD), U31.39 (DVDD), U31.50 (VREG_FB)
+3.3VA: C19.1, U31.44 (ADC_AVDD); also elsewhere on the board
+3V3: C1.1, C5.1, C10.1, C11.1, C12.1, C13.1, C14.1, C15.1, C16.1, C17.1, C18.1, R2.1, U31.1 (IOVDD), U31.11 (IOVDD), U31.20 (IOVDD), U31.30 (IOVDD), U31.38 (IOVDD), U31.45 (IOVDD), U31.49 (VREG_VIN), U31.53 (USB_OTP_VDD), U31.54 (QSPI_IOVDD), U32.8 (VCC); also elsewhere on the board
ADC_DET_A: U31.42 (GPIO28_ADC2); also elsewhere on the board
ADC_DET_B: U31.43 (GPIO29_ADC3); also elsewhere on the board
ADC_KEY_A: U31.40 (GPIO26_ADC0); also elsewhere on the board
ADC_KEY_B: U31.41 (GPIO27_ADC1); also elsewhere on the board
BANK_ID0: U31.5 (GPIO3); also elsewhere on the board
BANK_ID1: U31.7 (GPIO4); also elsewhere on the board
BOOTSEL_R: R3.1, SW1.2
BUS_DE: U31.4 (GPIO2); also elsewhere on the board
BUS_RX: U31.3 (GPIO1); also elsewhere on the board
BUS_TX: U31.2 (GPIO0); also elsewhere on the board
GND: C1.2, C2.2, C3.2, C4.2, C5.2, C6.2, C7.2, C8.2, C9.2, C10.2, C11.2, C12.2, C13.2, C14.2, C15.2, C16.2, C17.2, C18.2, C19.2, D1.1 (K), J1.2, J2.4, R4.2, SW1.1, U31.47 (VREG_PGND), U31.61 (GND), U32.4 (GND), Y1.2, Y1.4; also elsewhere on the board
LED_DATA: U31.14 (GPIO10); also elsewhere on the board
MUX_S0: U31.9 (GPIO6); also elsewhere on the board
MUX_S1: U31.10 (GPIO7); also elsewhere on the board
MUX_S2: U31.12 (GPIO8); also elsewhere on the board
MUX_S3: U31.13 (GPIO9); also elsewhere on the board
QSPI_SCLK: U31.56 (QSPI_SCLK), U32.6 (CLK)
QSPI_SD0: U31.57 (QSPI_SD0), U32.5 (DI(IO0))
QSPI_SD1: U31.59 (QSPI_SD1), U32.2 (DO(IO1))
QSPI_SD2: U31.58 (QSPI_SD2), U32.3 (IO2)
QSPI_SD3: U31.55 (QSPI_SD3), U32.7 (IO3)
QSPI_SS: R3.2, U31.60 (QSPI_SS), U32.1 (~CS)
RUN: SW2.2, U31.26 (RUN)
RUN_R: R4.1, SW2.1
STATUS_LED: R7.1, U31.37 (GPIO25)
STATUS_LED_R: D1.2 (A), R7.2
SWCLK: J1.1, U31.24 (SWCLK)
SWDIO: J1.3, U31.25 (SWD)
USB_DM: J2.2, R5.2
USB_DM_MCU: R5.1, U31.51 (USB_DM)
USB_DP: J2.3, R6.2
USB_DP_MCU: R6.1, U31.52 (USB_DP)
VREG_AVDD: C4.1, R2.2, U31.46 (VREG_AVDD)
VREG_LX: L1.1, U31.48 (VREG_LX)
XIN: C2.1, U31.21 (XIN), Y1.1
XOUT: R1.1, U31.22 (XOUT)
XTAL_OUT: C3.1, R1.2, Y1.3

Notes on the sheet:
GPIO map: GPIO0 BUS_TX (UART0), GPIO1 BUS_RX, GPIO2 BUS_DE, GPIO3/4 BANK_ID0/1, GPIO6-9 MUX_S0-S3, GPIO10 LED_DATA, GPIO25 STATUS_LED, GPIO26-29 ADC: KEY_A, KEY_B, DET_A, DET_B. Unused GPIO are flagged no-connect. ADC_AVDD is on +3.3VA, the same rail as the sensors and muxes, so the ADC reference t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
Core regulator, from Raspberry Pi's RP2350A minimal design: L1 3.3 uH polarised 2016 inductor (keep the dot orientation of the footprint), R2/C4 filter VREG_AVDD.
Decoupling: C10-C17 one per IOVDD / QSPI_IOVDD / USB_OTP_VDD pin, C18 bulk, C19 at ADC_AVDD.
J1: Raspberry Pi 3-pin debug connector (JST SH), for the Debug Probe.
J2: USB for bench bring-up and UF2 flashing (pin 1 VBUS not used; the bank is powered from +12V).

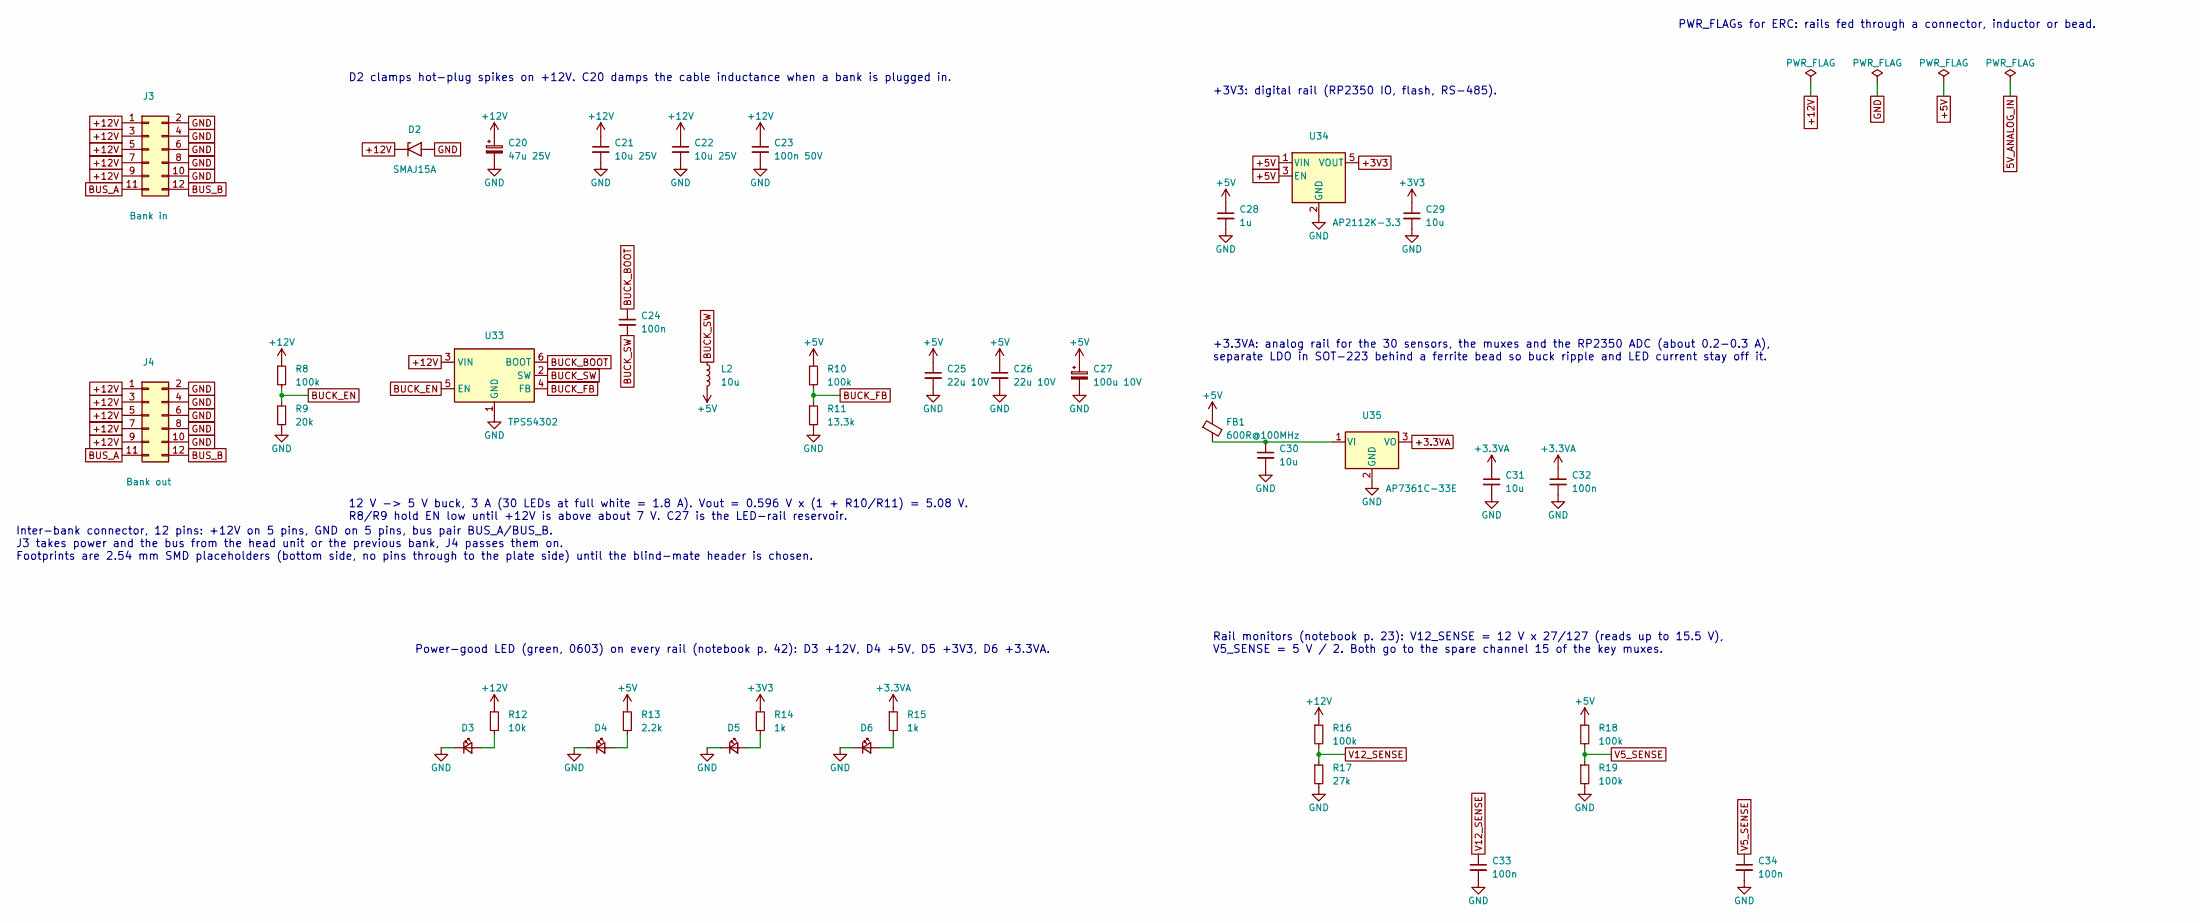
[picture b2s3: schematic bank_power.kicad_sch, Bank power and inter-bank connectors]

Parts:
C20: 47u 25V; CP_Elec_6.3x7.7
C21, C22: 10u 25V; C_1206_3216Metric
C23: 100n 50V; C_0402_1005Metric
C24, C32, C33, C34: 100n; C_0402_1005Metric
C25, C26: 22u 10V; C_1206_3216Metric
C27: 100u 10V; CP_Elec_6.3x7.7
C28: 1u; C_0402_1005Metric
C29, C30, C31: 10u; C_0805_2012Metric
D2: SMAJ15A; D_SMA
D3, D4, D5, D6: green; LED_0603_1608Metric
FB1: 600R@100MHz; L_0805_2012Metric
J3: Bank in; PinSocket_2x06_P2.54mm_Vertical_SMD
J4: Bank out; PinHeader_2x06_P2.54mm_Vertical_SMD
L2: 10u; L_Bourns_SRN6045TA
R8, R10, R16, R18, R19: 100k; R_0402_1005Metric
R9: 20k; R_0402_1005Metric
R11: 13.3k; R_0402_1005Metric
R12: 10k; R_0402_1005Metric
R13: 2.2k; R_0402_1005Metric
R14, R15: 1k; R_0402_1005Metric
R17: 27k; R_0402_1005Metric
U33: TPS54302; SOT-23-6
U34: AP2112K-3.3; SOT-23-5
U35: AP7361C-33E; SOT-223-3_TabPin2

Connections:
+3.3VA: C31.1, C32.1, R15.1, U35.3 (VO); also elsewhere on the board
+3V3: C29.1, R14.1, U34.5 (VOUT); also elsewhere on the board
+5V: C25.1, C26.1, C27.1, C28.1, FB1.1, L2.2, R10.1, R13.1, R18.1, U34.1 (VIN), U34.3 (EN); also elsewhere on the board
+12V: C20.1, C21.1, C22.1, C23.1, D2.1 (A1), J3.1, J3.3, J3.5, J3.7, J3.9, J4.1, J4.3, J4.5, J4.7, J4.9, R8.1, R12.1, R16.1, U33.3 (VIN)
BUCK_BOOT: C24.1, U33.6 (BOOT)
BUCK_EN: R8.2, R9.1, U33.5 (EN)
BUCK_FB: R10.2, R11.1, U33.4 (FB)
BUCK_SW: C24.2, L2.1, U33.2 (SW)
BUS_A: J3.11, J4.11; also elsewhere on the board
BUS_B: J3.12, J4.12; also elsewhere on the board
GND: C20.2, C21.2, C22.2, C23.2, C25.2, C26.2, C27.2, C28.2, C29.2, C30.2, C31.2, C32.2, C33.2, C34.2, D2.2 (A2), D3.1 (K), D4.1 (K), D5.1 (K), D6.1 (K), J3.2, J3.4, J3.6, J3.8, J3.10, J4.2, J4.4, J4.6, J4.8, J4.10, R9.2, R11.2, R17.2, R19.2, U33.1 (GND), U34.2 (GND), U35.2 (GND); also elsewhere on the board
unnamed: D3.2 (A), R12.2
unnamed: D4.2 (A), R13.2
unnamed: D5.2 (A), R14.2
unnamed: D6.2 (A), R15.2
unnamed: C30.1, FB1.2, U35.1 (VI)
V5_SENSE: C34.1, R18.2, R19.1; also elsewhere on the board
V12_SENSE: C33.1, R16.2, R17.1; also elsewhere on the board

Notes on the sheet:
Inter-bank connector, 12 pins: +12V on 5 pins, GND on 5 pins, bus pair BUS_A/BUS_B. J3 takes power and the bus from the head unit or the previous bank, J4 passes them on. Footprints are 2.54 mm SMD placeholders (bottom side, no pins through to the plate side) until the blind-mate header is chosen.
D2 clamps hot-plug spikes on +12V. C20 damps the cable inductance when a bank is plugged in.
12 V -> 5 V buck, 3 A (30 LEDs at full white = 1.8 A). Vout = 0.596 V x (1 + R10/R11) = 5.08 V. R8/R9 hold EN low until +12V is above about 7 V. C27 is the LED-rail reservoir.
+3V3: digital rail (RP2350 IO, flash, RS-485).
+3.3VA: analog rail for the 30 sensors, the muxes and the RP2350 ADC (about 0.2-0.3 A), separate LDO in SOT-223 behind a ferrite bead so buck ripple and LED current stay off it.
Power-good LED (green, 0603) on every rail (notebook p. 42): D3 +12V, D4 +5V, D5 +3V3, D6 +3.3VA.
Rail monitors (notebook p. 23): V12_SENSE = 12 V x 27/127 (reads up to 15.5 V), V5_SENSE = 5 V / 2. Both go to the spare channel 15 of the key muxes.
PWR_FLAGs for ERC: rails fed through a connector, inductor or bead.
